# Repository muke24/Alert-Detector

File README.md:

Made for fun. I'd love for likeminded individuals to help with this project. I've been working on this idea for 3 years on and off, so make good use of it.

----------------------------------------
Description:

This project was inspired by the original Need for Speed Most Wanted (2005) which includes a device that uses Waze alert data which currently only points towards the closest police car. A really cool project which scrapes Waze API alert data (currently only POLICE alerts) and displays an arrow pointing towards the closest alert. It also shows the heat level, determined by how many police alerts are in the area. Along with that, the icon for the alert which was detected is also displayed, so if there are 3 police cars in the vicinity then 3 police icons will be shown.
The distance of the closest alert is also shown. Alert submission back to Waze does not exist, but if someone figured out how to, that would be cool.

This used to work perfectly, and if you use the Waze URL found within the code and paste it in to your search bar, you'll still see the JSON containing all of the alerts.
I think Waze may have patched this for devices which doesn't send cookie data, like this ESP32, but with some hacking around I think someone could get past this.
This code can be found in "Code/1_75 Inch/AlertFinder/AlertRetriever.cpp". Keep in mind this is a Waze backdoor API URL, use at your own risk. This could be changed at any time which it seems that some sort of security with it has changed and has not been working recently with the ESP32's I have tested recently. It still works within a Unity application as of currently - https://github.com/muke24/Civic_03

Uses DIY knob as inspiration found at https://github.com/scottbez1/smartknob. The youtube video I followed was: https://www.youtube.com/watch?v=ip641WmY4pA.
I used this as I did not want a cheap feel to the device, and makes it more premium and is stronger than a regular rotary encoder like an EC35 rotary encoder.
I also did not want to explicitly use touch, as touch screens and cars don't work well together in my humble opinion, so I wanted to use the touch screen as a sensor to know when the knob is pushed down, which would in theory make a haptic like vibration to replicate a button press. This has not been completed, but that was the idea.

I'd love to add a dashcam functionality and even AI detection of alerts, however the current device runs at about 15 frames per second, so this is not viable with this setup.
A Jetson Nano should do that job well, but that would get expensive. Definitely something I want to make though.

----------------------------------------

Data Source Warning: 
The device currently uses a reverse-engineered, non-public Waze URL. 
This method is fragile and likely violates Waze's Terms of Service. The URL is currently broken for the device (unsure of why, it works perfectly within Unity and it DID used to work on this ESP32, one day it just stopped working, not sure exactly what it is related to but AI told me its something to do with cookies, so there is a head start, maybe I just missed something, and if not I can already think of a few dodgy work arounds eg. get a server to pull the data instead and then get this device to pull from the server), 
so the first challenge for the community is to fix the access method. All code is provided under the MIT license."

----------------------------------------

PCB Warning:
PCB is untested. It is used to connect the ESP32 to the modules and power management. The ESP32 connects to this PCB by feeding 28AUG enameled copper wires through the hollow shaft motor. Do not hot glue the enamelled wires directly to the ESP32, but solder them onto the end of a 8 pin male header and push that into the device, seems to work pretty well.

----------------------------------------

Files for Creation

- Code: "Code/1_75 Inch/AlertFinder.ino"
- Models: "Models/13" (Read the README file in Models folder)
- PCB Files: PCB/1_75/kiCadWiringDiagram2025aug29/kiCadWiringDiagram

Parts: 
- ESP32: Waveshare 1.75Inch AMOLED ESP32-S3 (with GPS and Speaker) - https://www.waveshare.com/esp32-s3-touch-amoled-1.75.htm
- LED: (48leds used) 160 LEDs/m WS2812B 2.7mm width - https://www.aliexpress.com/item/1005006697141669.html?spm=a2g0o.order_list.order_list_main.172.643b18023ERucf
- Motor: 2804 iFlight Ipower - https://www.aliexpress.com/item/1005008389835260.html?spm=a2g0o.order_list.order_list_main.67.7c741802dJIMvc
(will test cheaper model eventually, I received 3 different types, there was a cheaper one that would have worked with some modeling work to add an encoder {https://www.aliexpress.com/item/4001123251754.html?spm=a2g0o.order_list.order_list_main.77.7c741802dJIMvc} but I received the iFlight first)
- PCB (To be sent to manufacturer JLCPCB)
- 28AUG Enamelled Wire
- 8 pin 2.54mm male header
- 10 Pin JST XH male header

On PCB:
- Magnetometer: MMC5883 (on PCB)
- Motor controller: TMC6300-LA (Might be changed on PCB if no stock is available)

M2 screws used.

----------------------------------------

TODO:

- Remove wire tray from "15" model and rename that to "16". (It was added to test things before I got a PCB manufactured, but even the tray was never used, so will need to fix that up)
- Code haptics and knob control for the motor
- Code LED's
- Code the magnetometer (merge the MMC5883 with the built-in 6 axis IMU on the Waveshare device to create a 9-axis IMU so that compass will work accurately)
- Code other Waze alerts and subtypes
- Code user settings so that brightness / selected alerts / ect can be modified
- Model universal mirror mounts so that the device can be held in place

Untested:
I have not yet manufactured a PCB.
I have not tested or coded the motor functionality. The motor will be used for haptics, and knob rotation feedback and selecting options such as changing alerts, brightness ect (not coded yet but you get the idea).
LED's have not yet been tested.
Pretty much anything connecting to the PCB hasn't been tested yet. I do however have coded all of these functions (except motor function) on the old version of this device (in the "Old" folder).

I do not want precise touch functionality, touch only exists to detect button presses. A mini touch screen makes no sense on a device made for use in a car to specifically reduce the need to even look at the Waze app for alert info.

I did make a different version with different parts. It was ugly and no model was made for it, but functionally it worked entirely (encoder worked, LED's worked and would flash at a speed dependant on how far the closest alert was, GUI was functional but showed no colour and was ugly, the arrow pointed at the closest police alert, speaker made OG NFSMW radar sounds which also played repeatedly dependant on how far the closest alert was). This can be found somewhere in the "Old" folder. I've provided Google Drive links with videos of the old version working with real alerts.

----------------------------------------

Additional Remarks:

If I were to pick and choose any future ideas, I would do this -

Models
Multiple models with differing price ranges:
- Cheapest: 1.46i Waveshare AMOLED with regular rotary encoder. Similar design to how it is now but cheaper and simpler. (Around $120 AUD)
- Mid Range: 1.75i Waveshare AMOLED (this design) but with added dashcam functionality. (Around $275 AUD)
- Flagship: 1.75i AMOLED using Nvidia Jetson Nano with dashcam and AI alert auto detection (Around a steap $850 AUD). (I know this is pretty ambitious, wanna team up Waze?)

Software
- A phone app to change settings and view dashcam videos if it were to be added. 
- AI Auto detection of alerts via camera.
- Alert Reporting

Hardware
- (Flagship) Dual PTZ Camera's for better long distance accuracy. LIDAR won't work through glass.
- (Flagship) Custom PCB built within the enclosure instead of the knob.

----------------------------------------

Pictures taken throughout development:

https://github.com/user-attachments/assets/8ef88b90-4c08-46e0-89e6-efae050536bf

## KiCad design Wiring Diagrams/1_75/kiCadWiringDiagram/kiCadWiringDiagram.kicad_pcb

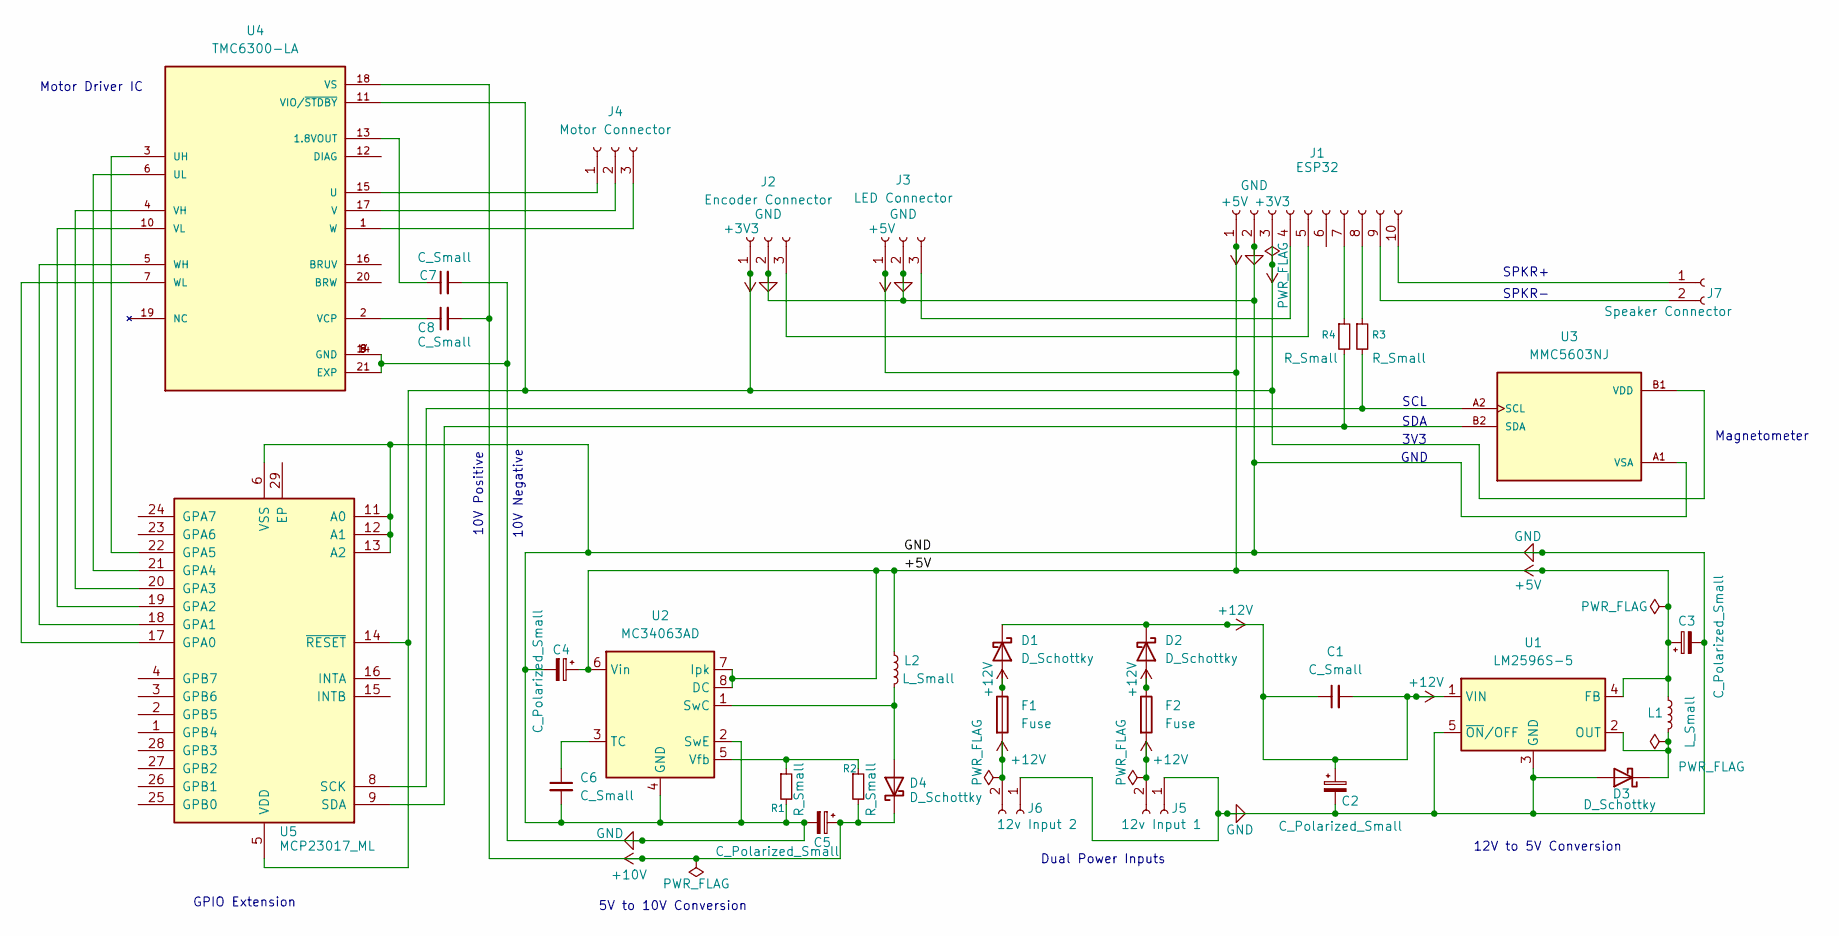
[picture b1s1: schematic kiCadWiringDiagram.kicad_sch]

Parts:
C1, C6, C7, C8: C_Small; C_0805_2012Metric
C2, C3, C4, C5: C_Polarized_Small; CP_Elec_6.3x5.4
D1, D2, D3, D4: D_Schottky; D_SMA
F1, F2: Fuse; Fuse_1206_3216Metric
J1: ESP32; JST_XH_S10B-XH-A-1_1x10_P2.50mm_Horizontal
J2: Encoder Connector; JST_XH_S3B-XH-A-1_1x03_P2.50mm_Horizontal
J3: LED Connector; JST_XH_S3B-XH-A-1_1x03_P2.50mm_Horizontal
J4: Motor Connector; JST_XH_S3B-XH-A-1_1x03_P2.50mm_Horizontal
J5: 12v Input 1; JST_XH_S2B-XH-A-1_1x02_P2.50mm_Horizontal
J6: 12v Input 2; JST_XH_S2B-XH-A-1_1x02_P2.50mm_Horizontal
J7: Speaker Connector; JST_GH_BM02B-GHS-TBT_1x02-1MP_P1.25mm_Vertical
L1, L2: L_Small; L_7.3x7.3_H4.5
R1, R2, R3, R4: R_Small; R_0805_2012Metric
U1: LM2596S-5; TO-263-5_TabPin3
U2: MC34063AD; SOIC-8_3.9x4.9mm_P1.27mm
U3: MMC5603NJ; XDCR_MMC5603NJ; PARTREV B
U4: TMC6300-LA; QFN40P300X300X90-21N; PARTREV 1.08
U5: MCP23017_ML; QFN-28-1EP_6x6mm_P0.65mm_EP4.25x4.25mm

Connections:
+3V3: J1.3, J2.1, U3.B1 (VDD), U4.11 (VIO/~STDBY), U5.5 (VDD), U5.14 (~RESET)
+5V: C3.1, C4.1, J1.1, J3.1, L1.1, L2.1, U1.4 (FB), U2.6 (Vin), U2.7 (Ipk), U2.8 (DC)
+10V: C5.1, C8.2, D4.1 (K), R2.2, U4.18 (VS)
+12V: C1.1, C1.2, C2.1, D1.1 (K), D1.2 (A), D2.1 (K), D2.2 (A), F1.1, F1.2, F2.1, F2.2, J5.2, J6.2, U1.1 (VIN)
GND: C2.2, C3.2, C4.2, C5.2, C6.2, C7.2, D3.2 (A), J1.2, J2.2, J3.2, J5.1, J6.1, R1.2, U1.3 (GND), U1.5 (~ON/OFF), U2.2 (SwE), U2.4 (GND), U3.A1 (VSA), U4.8 (GND), U4.9 (GND), U4.14 (GND), U4.21 (EXP), U5.6 (VSS), U5.11 (A0), U5.12 (A1), U5.13 (A2)
unnamed: D3.1 (K), L1.2, U1.2 (OUT)
unnamed: D4.2 (A), L2.2, U2.1 (SwC)
unnamed: J1.4, J3.3
unnamed: J1.5, J2.3
unnamed: J1.7, R4.1
unnamed: J1.8, R3.1
unnamed: J1.9, J7.2
unnamed: J1.10, J7.1
unnamed: J4.1, U4.15 (U)
unnamed: J4.2, U4.17 (V)
unnamed: J4.3, U4.1 (W)
unnamed: C6.1, U2.3 (TC)
unnamed: R1.1, R2.1, U2.5 (Vfb)
unnamed: R3.2, U3.A2 (SCL), U5.8 (SCK)
unnamed: R4.2, U3.B2 (SDA), U5.9 (SDA)
unnamed: C7.1, U4.13 (1.8VOUT)
unnamed: U4.3 (UH), U5.22 (GPA5)
unnamed: U4.6 (UL), U5.21 (GPA4)
unnamed: C8.1, U4.2 (VCP)
unnamed: U4.4 (VH), U5.20 (GPA3)
unnamed: U4.10 (VL), U5.19 (GPA2)
unnamed: U4.5 (WH), U5.18 (GPA1)
unnamed: U4.7 (WL), U5.17 (GPA0)

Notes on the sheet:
12V to 5V Conversion
3V3
GPIO Extension
5V to 10V Conversion
10V Negative
GND
Motor Driver IC
SPKR-
SDA
SCL
Dual Power Inputs
10V Positive
Magnetometer
SPKR+

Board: 2 copper layers, 32 parts (0 on the bottom side), 28 nets, no tracks yet.

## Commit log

2025-04-29 Alert Detector Start
2025-04-30 Still writing comments
2025-05-02 Model V1 Finished (PRP_07)
2025-05-03 Finished 3D Model
    Printable 3D model
2025-05-07 More planning
2025-05-07 Added specsheet
2025-05-07 Adjustments
2025-05-10 alert receiver GPS start
2025-05-10 LTE work
2025-05-18 More Work
2025-05-18 GPS and Compass (BNO08X)
2025-05-18 GPS Script: Working script with NEO-M8N and Waze Alert retrieval
2025-05-18 GPS Script: FUNCTIONALITY WORKING
    No LTE or data output, however the code outputs the closest police alert found and prints out its relative angle from us.
2025-05-18 Relative angle data is being sent
    Plug in GPIO18 (TX) to GPIO19 (RX) to debug the data being sent to other ESP device
2025-05-18 Code reorganisation
    Detailed code comments added and reorganisation of the code for better clarity
2025-05-18 File reorganisation work
2025-05-19 V1 Wiring Diagram
2025-05-21 3D Model Work
2025-05-24 GPS testing
2025-05-26 hmc5883l test
2025-05-26 Working script with HMC5883L
2025-05-26 Successful loopback test for ESP32 communication
2025-05-26 working loopback in AlertFinder script
2025-05-26 renderer test
2025-05-27 more work and testing
2025-05-27 testing
2025-05-27 Success with 10 pin FPC Extender
    Issue was with extension board hardware which came with the Viewe 1.28 inch display. We can order a 10pin FPC 0.5mm extension board to replace it at: https://vi.aliexpress.com/item/1005007145462021.h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
2025-05-27 3D print fixed
2025-05-27 Successful LED Test
2025-05-27 LED Success
2025-05-27 Audio start
2025-05-28 Sound plays and sounds better
2025-05-28 Sound inconsistency fixed
2025-05-28 3D touchups and included lv_conf
2025-05-28 3D Model Functional
    Closer to end design. This design will likely be used for all of development if all dimensions are correct.
2025-05-29 Colours are showing correctly
2025-05-30 Hardcoded compass images
    Arrow not yet functional
2025-05-30 Arrow rotates nicely (WITH ISSUES)
    Has clipping. This is because there is not enough DRAM to display the canvas buffers at 154x154. 154x154 is required to keep arrow from clipping.
2025-05-31 AlertReceiver renamed + Folder organisation
    AlertReceiver renamed to AlertFinder
2025-05-31 Accidental pin change reversed
2025-05-31 Planning
2025-06-01 LED Fix + Planning
2025-06-02 Modelling
2025-06-02 Modelling work
2025-06-28 Code reorganisation
    Code has been split up into modules, so each physical module can have its own script.
    BNO086 came out to be a dead end. Whilst it seemed to work, after more research it seems it is too unreliable.
    Adafruit LSM6DSOX + LIS3MDL seems like the way to go, as it's newer and has been tested with aviation purposes with positive reviews.
    This code includes the last BNO086 implementation.
2025-07-23 Compass GUI for 1.75i + model
2025-07-25 GUI mostly done
    Just need to add other alert icons
2025-07-25 GUI fully functional
2025-07-25 Heatbar animations
2025-07-25 Heatbar animations perfected
2025-07-25 Distance Text empty when set to -1
    Distance label will now be empty when no alert is found (in demo)
2025-07-26 knob model
    needs adjusting but is a good start
2025-07-28 Adapter
    Adapter is still kinda weak, but will do for now. Still haven't tested with anything but PLA, that could be the issue but we'll see
2025-07-28 Splitting up scripts
2025-07-29 modeling + split scripts
2025-07-30 Printer settings
2025-07-30 messing around with compass
    compass not working yet
2025-08-01 Modeling + wiring diagram
2025-08-02 Adapter work
    trying to perfect. This might actually work with the stronger filament PETG, but is making PLA snap. Is a very good and tight fitment however
2025-08-06 More modelling
2025-08-09 Work on makeshift PCB
    3D modeling a PCB-like wiring harness and making a wiring diagram directly for it. Both have been started but still needs finishing.
    Change to using a 12v input with a 2.1mm barrel jack connector as power may exceed USB 2 speeds which we don't want. Also a direct connect for connecting directly to battery.
2025-08-12 Wiring work
2025-08-12 module holder/wiring harness work
2025-08-13 new part - gps holder
    Still needs work - need screw holes for gps holder to screw in to enclosure
2025-08-13 Screw holes for gps holder
2025-08-13 update
    Need to shorten enclosure and fix board shape
2025-08-13 prints
2025-08-14 Model GPS size fix
2025-08-14 Wiring
2025-08-17 Added wire trays
2025-08-21 Designing schematic
    Completed dual 12V inputs and converting them to 5V.
    The rest of the circuit still remains.
2025-08-21 5v to 10v conversion looks complete
    fixed polarized capacitors
2025-08-21 Schematic done I think
2025-08-21 need to add motor driver ic
2025-08-21 Needs IO expander as motor driver takes 6 GPIO pins
2025-08-21 Schematic now done I think
2025-08-21 pull up resisters added to i2c bus
    now finished schematic I think
2025-08-22 Started Footprint assignments
2025-08-22 Completed footprints
2025-08-22 started work on PCB
2025-10-22 Add project overview and future plans to README
    Added project description and inspiration details.
2025-10-22 Update README with project inspiration and future plans
    Clarified alert submission and dashcam functionality plans.
2025-10-22 Add MIT License to the project
2025-10-22 Update README with Waze and project inspiration details
    Added notes about Waze functionality and project inspiration.
2025-10-22 Update README with project pictures
    Expanded on project details, including parts sourcing and pictures of the device
2025-10-22 Fix typo
2025-10-22 Include pictures of the device in README
    Added a section for device pictures in the README.
2025-10-22 Update README with additional details
    Added random details about screws and versions.
2025-10-22 README
2025-10-24 File cleanup
2025-10-24 Revise README for clarity and project details
    Refactored README content for clarity and organization, removing redundant information and improving project description.
2025-10-24 Enhance README with PCB usage and component details
    Updated README with additional warnings and notes on PCB and components.
2025-10-24 Revise README with project details and future plans
    Updated project description and added details about future functionalities and current limitations. Removed some redundant information and clarified the use of the device.
2025-10-24 Add GitHub link and clarify API usage in README
    Updated README to include GitHub project link and clarify functionality.
2025-10-24 Update header description in README
    Clarified the description of the 8 pin male header in the README.
2025-10-24 Enhance README with project details and clarifications
    Expanded project description and clarified functionality details.
2025-10-24 Fix formatting README.md
2025-10-24 Expand README with future ideas and additional remarks
    Added additional remarks section with future ideas for models, software, and hardware enhancements.
2025-10-24 Update Waze data source warning in README
    Expanded explanation of the Waze URL access method and its issues.
2025-10-25 Update project description in README.md
    Reworded description for clarity and conciseness.
2025-10-25 Update wording in README for clarity
2025-10-25 README clarity
2025-10-25 Add task for modeling universal mirror mounts
    Added a task to model universal mirror mounts for device stability.
